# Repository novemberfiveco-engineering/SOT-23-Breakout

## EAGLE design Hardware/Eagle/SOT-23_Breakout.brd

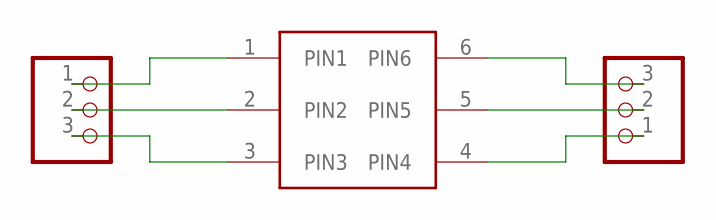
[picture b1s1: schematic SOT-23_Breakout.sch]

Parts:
.: SOT-23-6
JP1, JP2: PINHD-1X3; 1X03

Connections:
unnamed: ..1 (PIN1), JP1.1
unnamed: ..2 (PIN2), JP1.2
unnamed: ..3 (PIN3), JP1.3
unnamed: ..6 (PIN6), JP2.3
unnamed: ..5 (PIN5), JP2.2
unnamed: ..4 (PIN4), JP2.1

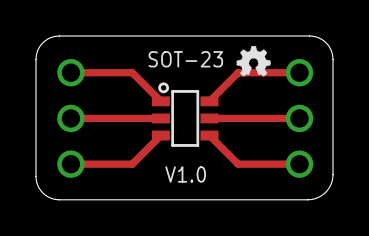
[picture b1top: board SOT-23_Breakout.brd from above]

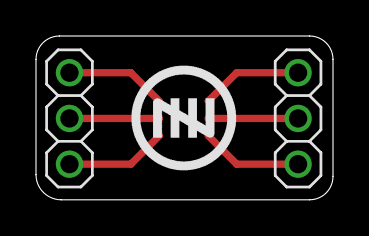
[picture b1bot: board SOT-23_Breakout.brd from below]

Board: 2 copper layers, 16.5 x 9.1 mm, 5 parts (2 on the bottom side), 6 nets.

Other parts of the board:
U$1: LOGO-OSHWA
U$2: LOGO-NOVEMERFIVE-7SCALE

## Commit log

2017-05-15 Added project library

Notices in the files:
parts and their libraries:
SparkFun-Aesthetics: Licensing: Creative Commons ShareAlike 4.0 International - https://creativecommons.org/licenses/by-sa/4.0
